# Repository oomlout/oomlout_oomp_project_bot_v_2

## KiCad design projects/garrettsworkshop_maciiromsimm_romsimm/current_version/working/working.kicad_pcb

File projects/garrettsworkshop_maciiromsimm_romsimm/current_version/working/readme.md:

# maciiromsimm
 
## summary 
* id: garrettsworkshop_maciiromsimm_romsimm
* user: garrettsworkshop
* name: maciiromsimm
* board: romsimm
* repo: https://github.com/garrettsworkshop/MacIIROMSIMM
* src_file_repo_kicad_pcb: ROMSIMM.kicad_pcb
* src_file_repo_kicad_pcb_link: https://github.com/garrettsworkshop/MacIIROMSIMM/tree/release-4402A/ROMSIMM.kicad_pcb

* src_file_repo_sch: ROMSIMM.sch
* src_file_repo_sch_link: https://github.com/garrettsworkshop/MacIIROMSIMM/tree/release-4402A/ROMSIMM.sch
* full details link: https://github.com/oomlout/oomlout_oomp_project_bot_v_2/tree/main/projects/garrettsworkshop_maciiromsimm_romsimm/current_version/working

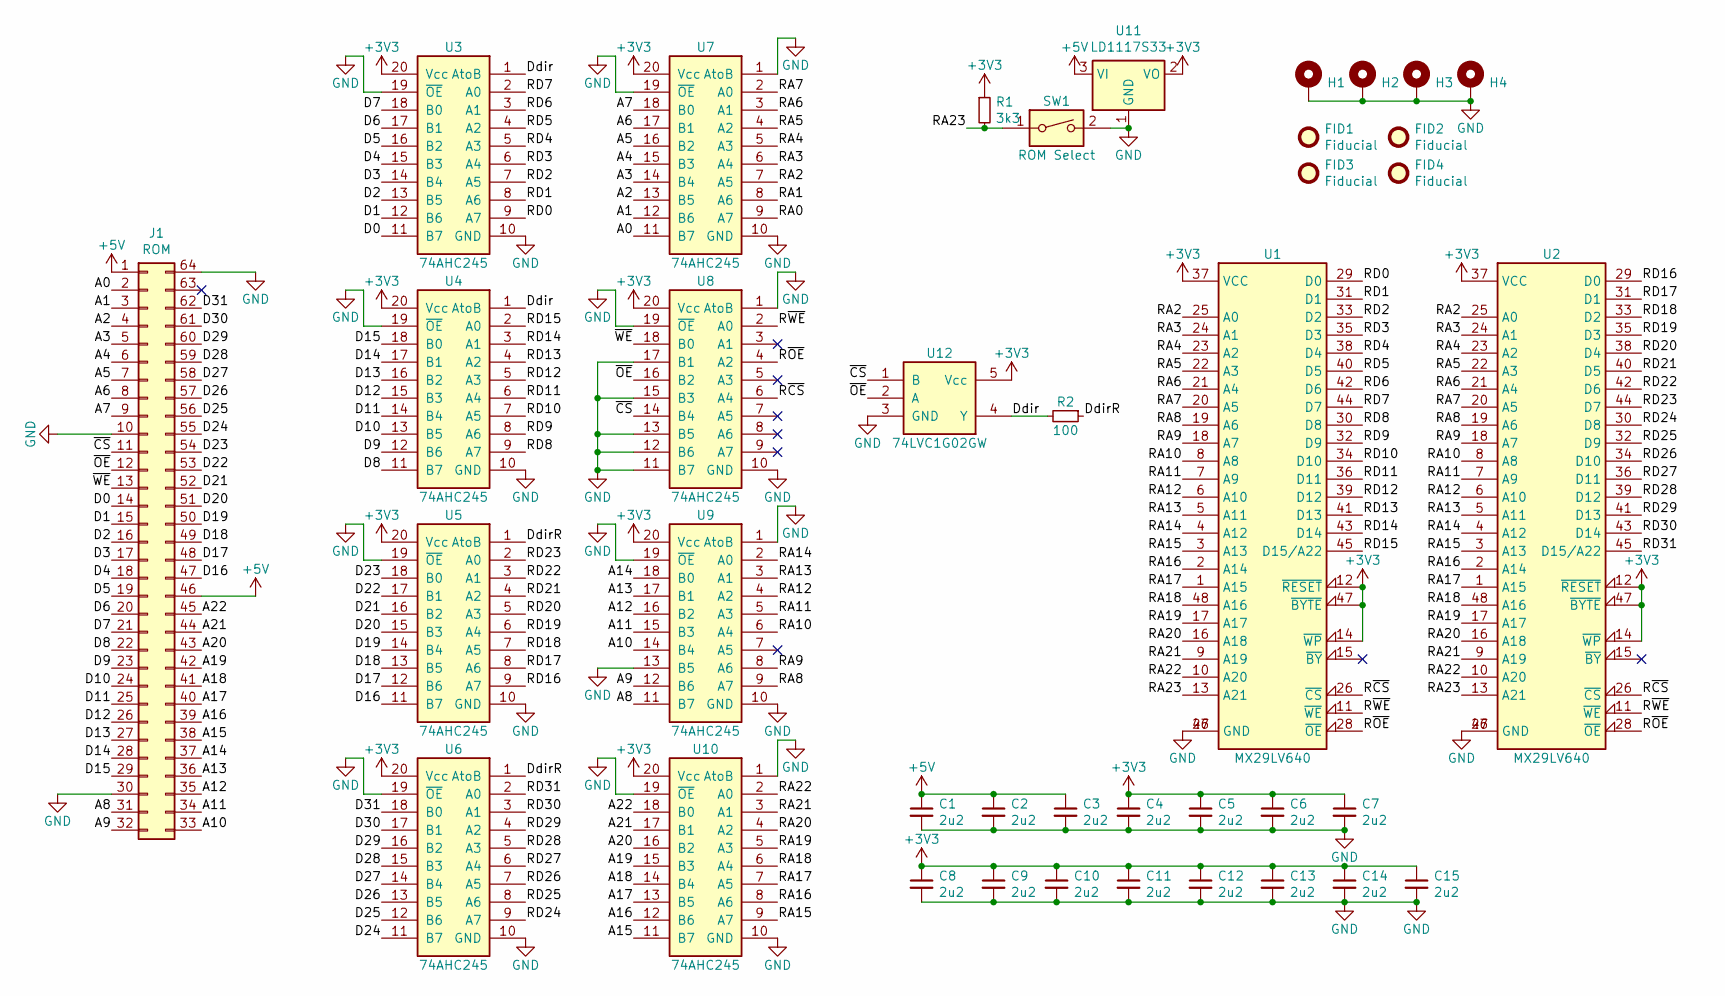
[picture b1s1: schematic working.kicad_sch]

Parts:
C1, C2, C3, C4, C5, C6, C7, C8, C9, C10, C11, C12, C13, C14, C15: 2u2; C_0603
FID1, FID2, FID3, FID4: Fiducial
H1, H2, H3, H4: PasteHole_1.1mm_PTH
J1: ROM; MacIIROMSIMM_Edge
R1: 3k3; R_0805
R2: 100; R_0805
SW1: ROM Select; SW_DIP_SPSTx01_Slide_6.7x4.1mm_W8.61mm_P2.54mm_LowProfile
U1, U2: MX29LV640; TSOP-I-48_18.4x12mm_P0.5mm
U3, U4, U5, U6, U7, U8, U9, U10: 74AHC245; TSSOP-20_4.4x6.5mm_P0.65mm
U11: LD1117S33; SOT-223
U12: 74LVC1G02GW; SOT-353

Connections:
+3V3: C4.1, C5.1, C6.1, C7.1, C8.1, C9.1, C10.1, C11.1, C12.1, C13.1, C14.1, C15.1, R1.1, U1.12 (~RESET), U1.14 (~WP), U1.37 (VCC), U1.47 (~BYTE), U2.12 (~RESET), U2.14 (~WP), U2.37 (VCC), U2.47 (~BYTE), U3.20 (Vcc), U4.20 (Vcc), U5.20 (Vcc), U6.20 (Vcc), U7.20 (Vcc), U8.20 (Vcc), U9.20 (Vcc), U10.20 (Vcc), U11.2 (VO), U12.5 (Vcc)
+5V: C1.1, C2.1, C3.1, J1.1, J1.46, U11.3 (VI)
/A0: J1.2, U7.11 (B7)
/A1: J1.3, U7.12 (B6)
/A2: J1.4, U7.13 (B5)
/A3: J1.5, U7.14 (B4)
/A4: J1.6, U7.15 (B3)
/A5: J1.7, U7.16 (B2)
/A6: J1.8, U7.17 (B1)
/A7: J1.9, U7.18 (B0)
/A8: J1.31, U9.11 (B7)
/A9: J1.32, U9.12 (B6)
/A10: J1.33, U9.14 (B4)
/A11: J1.34, U9.15 (B3)
/A12: J1.35, U9.16 (B2)
/A13: J1.36, U9.17 (B1)
/A14: J1.37, U9.18 (B0)
/A15: J1.38, U10.11 (B7)
/A16: J1.39, U10.12 (B6)
/A17: J1.40, U10.13 (B5)
/A18: J1.41, U10.14 (B4)
/A19: J1.42, U10.15 (B3)
/A20: J1.43, U10.16 (B2)
/A21: J1.44, U10.17 (B1)
/A22: J1.45, U10.18 (B0)
/D0: J1.14, U3.11 (B7)
/D1: J1.15, U3.12 (B6)
/D2: J1.16, U3.13 (B5)
/D3: J1.17, U3.14 (B4)
/D4: J1.18, U3.15 (B3)
/D5: J1.19, U3.16 (B2)
/D6: J1.20, U3.17 (B1)
/D7: J1.21, U3.18 (B0)
/D8: J1.22, U4.11 (B7)
/D9: J1.23, U4.12 (B6)
/D10: J1.24, U4.13 (B5)
/D11: J1.25, U4.14 (B4)
/D12: J1.26, U4.15 (B3)
/D13: J1.27, U4.16 (B2)
/D14: J1.28, U4.17 (B1)
/D15: J1.29, U4.18 (B0)
/D16: J1.47, U5.11 (B7)
/D17: J1.48, U5.12 (B6)
/D18: J1.49, U5.13 (B5)
/D19: J1.50, U5.14 (B4)
/D20: J1.51, U5.15 (B3)
/D21: J1.52, U5.16 (B2)
/D22: J1.53, U5.17 (B1)
/D23: J1.54, U5.18 (B0)
/D24: J1.55, U6.11 (B7)
/D25: J1.56, U6.12 (B6)
/D26: J1.57, U6.13 (B5)
/D27: J1.58, U6.14 (B4)
/D28: J1.59, U6.15 (B3)
/D29: J1.60, U6.16 (B2)
/D30: J1.61, U6.17 (B1)
/D31: J1.62, U6.18 (B0)
/Ddir: R2.2, U3.1 (AtoB), U4.1 (AtoB), U12.4 (Y)
/DdirR: R2.1, U5.1 (AtoB), U6.1 (AtoB)
/RA0: U7.9 (A7)
/RA1: U7.8 (A6)
/RA2: U1.25 (A0), U2.25 (A0), U7.7 (A5)
/RA3: U1.24 (A1), U2.24 (A1), U7.6 (A4)
/RA4: U1.23 (A2), U2.23 (A2), U7.5 (A3)
/RA5: U1.22 (A3), U2.22 (A3), U7.4 (A2)
/RA6: U1.21 (A4), U2.21 (A4), U7.3 (A1)
/RA7: U1.20 (A5), U2.20 (A5), U7.2 (A0)
/RA8: U1.19 (A6), U2.19 (A6), U9.9 (A7)
/RA9: U1.18 (A7), U2.18 (A7), U9.8 (A6)
/RA10: U1.8 (A8), U2.8 (A8), U9.6 (A4)
/RA11: U1.7 (A9), U2.7 (A9), U9.5 (A3)
/RA12: U1.6 (A10), U2.6 (A10), U9.4 (A2)
/RA13: U1.5 (A11), U2.5 (A11), U9.3 (A1)
/RA14: U1.4 (A12), U2.4 (A12), U9.2 (A0)
/RA15: U1.3 (A13), U2.3 (A13), U10.9 (A7)
/RA16: U1.2 (A14), U2.2 (A14), U10.8 (A6)
/RA17: U1.1 (A15), U2.1 (A15), U10.7 (A5)
/RA18: U1.48 (A16), U2.48 (A16), U10.6 (A4)
/RA19: U1.17 (A17), U2.17 (A17), U10.5 (A3)
/RA20: U1.16 (A18), U2.16 (A18), U10.4 (A2)
/RA21: U1.9 (A19), U2.9 (A19), U10.3 (A1)
/RA22: U1.10 (A20), U2.10 (A20), U10.2 (A0)
/RA23: R1.2, SW1.1, U1.13 (A21), U2.13 (A21)
/RD0: U1.29 (D0), U3.9 (A7)
/RD1: U1.31 (D1), U3.8 (A6)
/RD2: U1.33 (D2), U3.7 (A5)
/RD3: U1.35 (D3), U3.6 (A4)
/RD4: U1.38 (D4), U3.5 (A3)
/RD5: U1.40 (D5), U3.4 (A2)
/RD6: U1.42 (D6), U3.3 (A1)
/RD7: U1.44 (D7), U3.2 (A0)
/RD8: U1.30 (D8), U4.9 (A7)
/RD9: U1.32 (D9), U4.8 (A6)
/RD10: U1.34 (D10), U4.7 (A5)
/RD11: U1.36 (D11), U4.6 (A4)
/RD12: U1.39 (D12), U4.5 (A3)
/RD13: U1.41 (D13), U4.4 (A2)
/RD14: U1.43 (D14), U4.3 (A1)
/RD15: U1.45 (D15/A22), U4.2 (A0)
/RD16: U2.29 (D0), U5.9 (A7)
/RD17: U2.31 (D1), U5.8 (A6)
/RD18: U2.33 (D2), U5.7 (A5)
/RD19: U2.35 (D3), U5.6 (A4)
/RD20: U2.38 (D4), U5.5 (A3)
/RD21: U2.40 (D5), U5.4 (A2)
/RD22: U2.42 (D6), U5.3 (A1)
/RD23: U2.44 (D7), U5.2 (A0)
/RD24: U2.30 (D8), U6.9 (A7)
/RD25: U2.32 (D9), U6.8 (A6)
/RD26: U2.34 (D10), U6.7 (A5)
/RD27: U2.36 (D11), U6.6 (A4)
/RD28: U2.39 (D12), U6.5 (A3)
/RD29: U2.41 (D13), U6.4 (A2)
/RD30: U2.43 (D14), U6.3 (A1)
/RD31: U2.45 (D15/A22), U6.2 (A0)
/R~CS: U1.26 (~CS), U2.26 (~CS), U8.6 (A4)
/R~OE: U1.28 (~OE), U2.28 (~OE), U8.4 (A2)
/R~WE: U1.11 (~WE), U2.11 (~WE), U8.2 (A0)
/~CS: J1.11, U8.14 (B4), U12.1 (B)
/~OE: J1.12, U8.16 (B2), U12.2 (A)
/~WE: J1.13, U8.18 (B0)
GND: C1.2, C2.2, C3.2, C4.2, C5.2, C6.2, C7.2, C8.2, C9.2, C10.2, C11.2, C12.2, C13.2, C14.2, C15.2, H1.1, H2.1, H3.1, H4.1, J1.10, J1.30, J1.64, SW1.2, U1.27 (GND), U1.46 (GND), U2.27 (GND), U2.46 (GND), U3.10 (GND), U3.19 (~OE), U4.10 (GND), U4.19 (~OE), U5.10 (GND), U5.19 (~OE), U6.10 (GND), U6.19 (~OE), U7.1 (AtoB), U7.10 (GND), U7.19 (~OE), U8.1 (AtoB), U8.10 (GND), U8.11 (B7), U8.12 (B6), U8.13 (B5), U8.15 (B3), U8.17 (B1), U8.19 (~OE), U9.1 (AtoB), U9.10 (GND), U9.13 (B5), U9.19 (~OE), U10.1 (AtoB), U10.10 (GND), U10.19 (~OE), U11.1 (GND), U12.3 (GND)

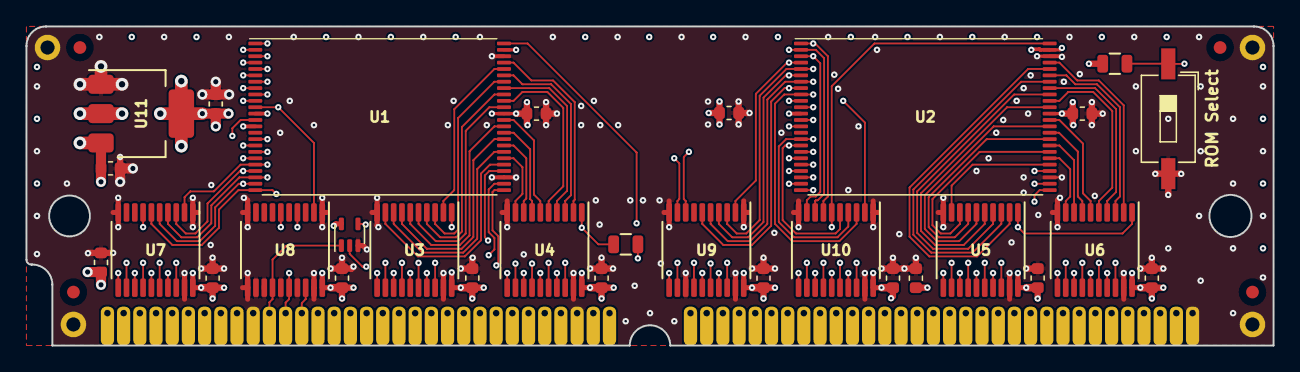
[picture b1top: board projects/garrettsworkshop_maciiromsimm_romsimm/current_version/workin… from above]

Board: 4 copper layers, 97.8 x 25.0 mm, 39 parts (0 on the bottom side), 120 nets.

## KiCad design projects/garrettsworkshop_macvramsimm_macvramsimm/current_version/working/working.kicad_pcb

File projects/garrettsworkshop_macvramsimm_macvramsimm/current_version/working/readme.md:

# macvramsimm
 
## summary 
* id: garrettsworkshop_macvramsimm_macvramsimm
* user: garrettsworkshop
* name: macvramsimm
* board: macvramsimm
* repo: https://github.com/garrettsworkshop/MacVRAMSIMM
* src_file_repo_kicad_pcb: 512kB-2chip-SOJ/MacVRAMSIMM.kicad_pcb
* src_file_repo_kicad_pcb_link: https://github.com/garrettsworkshop/MacVRAMSIMM/tree/dev/512kB-2chip-SOJ/MacVRAMSIMM.kicad_pcb
* src_file_repo_kicad_sch: 512kB-2chip-SOJ/MacVRAMSIMM.kicad_sch
* src_file_repo_kicad_sch_link: https://github.com/garrettsworkshop/MacVRAMSIMM/tree/dev/512kB-2chip-SOJ/MacVRAMSIMM.kicad_sch

* src_file_repo_sch: 256kB-2chip-SOJ/MacVRAMSIMM.sch
* src_file_repo_sch_link: https://github.com/garrettsworkshop/MacVRAMSIMM/tree/dev/256kB-2chip-SOJ/MacVRAMSIMM.sch
* full details link: https://github.com/oomlout/oomlout_oomp_project_bot_v_2/tree/main/projects/garrettsworkshop_macvramsimm_macvramsimm/current_version/working

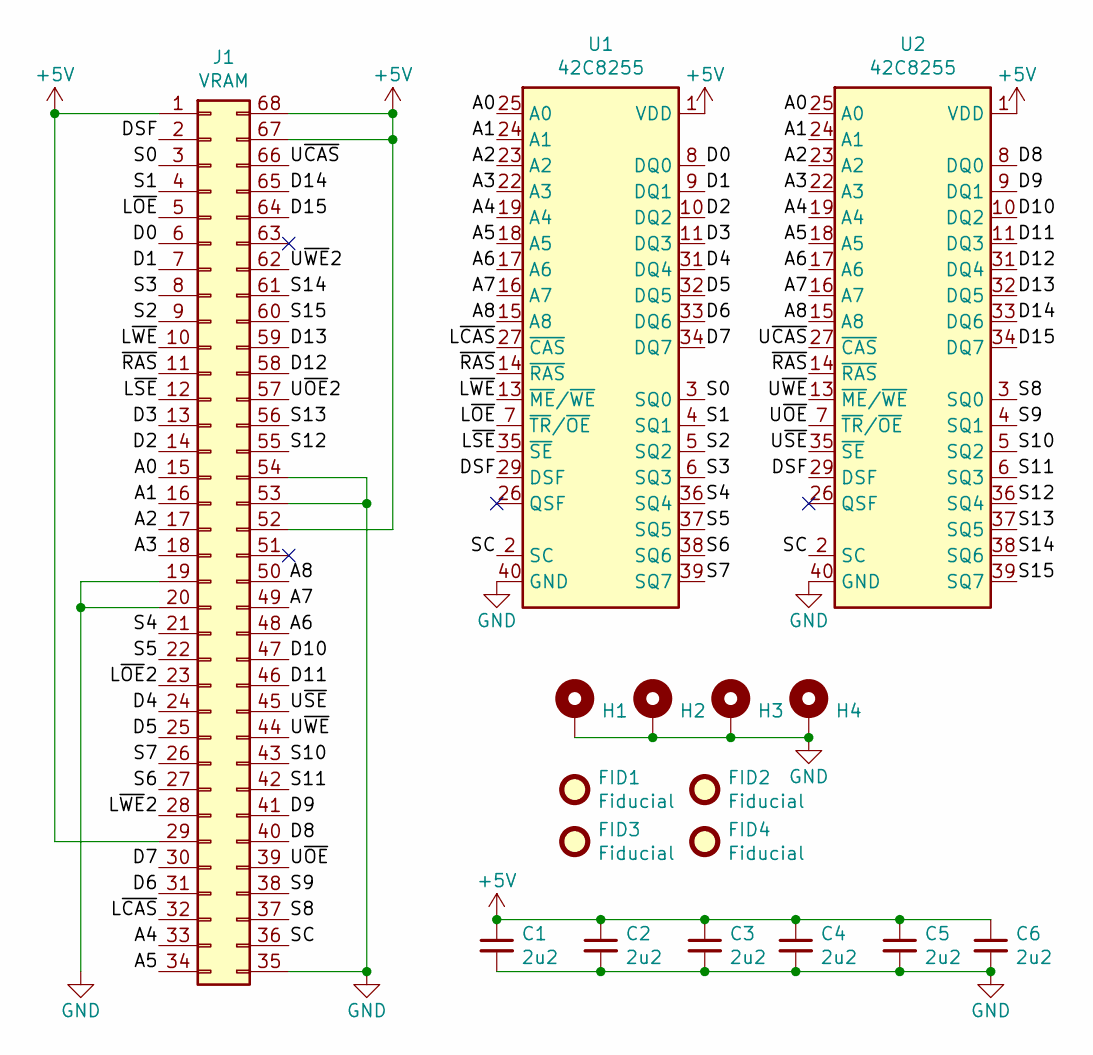
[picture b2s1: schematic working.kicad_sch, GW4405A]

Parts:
C1, C2, C3, C4, C5, C6: 2u2; C_0805
FID1, FID2, FID3, FID4: Fiducial
H1, H2, H3, H4: PasteHole_1.1mm_PTH
J1: VRAM; MacVRAMSIMM_Edge
U1, U2: 42C8255; SOJ-40_400mil

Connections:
+5V: C1.1, C2.1, C3.1, C4.1, C5.1, C6.1, J1.1, J1.29, J1.52, J1.67, J1.68, U1.1 (VDD), U1.20 (VDD), U2.1 (VDD), U2.20 (VDD)
/A0: J1.15, U1.25 (A0), U2.25 (A0)
/A1: J1.16, U1.24 (A1), U2.24 (A1)
/A2: J1.17, U1.23 (A2), U2.23 (A2)
/A3: J1.18, U1.22 (A3), U2.22 (A3)
/A4: J1.33, U1.19 (A4), U2.19 (A4)
/A5: J1.34, U1.18 (A5), U2.18 (A5)
/A6: J1.48, U1.17 (A6), U2.17 (A6)
/A7: J1.49, U1.16 (A7), U2.16 (A7)
/A8: J1.50, U1.15 (A8), U2.15 (A8)
/D0: J1.6, U1.8 (DQ0)
/D1: J1.7, U1.9 (DQ1)
/D2: J1.14, U1.10 (DQ2)
/D3: J1.13, U1.11 (DQ3)
/D4: J1.24, U1.31 (DQ4)
/D5: J1.25, U1.32 (DQ5)
/D6: J1.31, U1.33 (DQ6)
/D7: J1.30, U1.34 (DQ7)
/D8: J1.40, U2.8 (DQ0)
/D9: J1.41, U2.9 (DQ1)
/D10: J1.47, U2.10 (DQ2)
/D11: J1.46, U2.11 (DQ3)
/D12: J1.58, U2.31 (DQ4)
/D13: J1.59, U2.32 (DQ5)
/D14: J1.65, U2.33 (DQ6)
/D15: J1.64, U2.34 (DQ7)
/DSF: J1.2, U1.29 (DSF), U2.29 (DSF)
/L~CAS: J1.32, U1.27 (~CAS)
/L~OE: J1.5, U1.7 (~TR/~OE)
/L~OE2: J1.23
/L~SE: J1.12, U1.35 (~SE)
/L~WE: J1.10, U1.13 (~ME/~WE)
/L~WE2: J1.28
/S0: J1.3, U1.3 (SQ0)
/S1: J1.4, U1.4 (SQ1)
/S2: J1.9, U1.5 (SQ2)
/S3: J1.8, U1.6 (SQ3)
/S4: J1.21, U1.36 (SQ4)
/S5: J1.22, U1.37 (SQ5)
/S6: J1.27, U1.38 (SQ6)
/S7: J1.26, U1.39 (SQ7)
/S8: J1.37, U2.3 (SQ0)
/S9: J1.38, U2.4 (SQ1)
/S10: J1.43, U2.5 (SQ2)
/S11: J1.42, U2.6 (SQ3)
/S12: J1.55, U2.36 (SQ4)
/S13: J1.56, U2.37 (SQ5)
/S14: J1.61, U2.38 (SQ6)
/S15: J1.60, U2.39 (SQ7)
/SC: J1.36, U1.2 (SC), U2.2 (SC)
/U~CAS: J1.66, U2.27 (~CAS)
/U~OE: J1.39, U2.7 (~TR/~OE)
/U~OE2: J1.57
/U~SE: J1.45, U2.35 (~SE)
/U~WE: J1.44, U2.13 (~ME/~WE)
/U~WE2: J1.62
/~RAS: J1.11, U1.14 (~RAS), U2.14 (~RAS)
GND: C1.2, C2.2, C3.2, C4.2, C5.2, C6.2, H1.1, H2.1, H3.1, H4.1, J1.19, J1.20, J1.35, J1.53, J1.54, U1.12 (GND), U1.21 (GND), U1.30 (GND), U1.40 (GND), U2.12 (GND), U2.21 (GND), U2.30 (GND), U2.40 (GND)

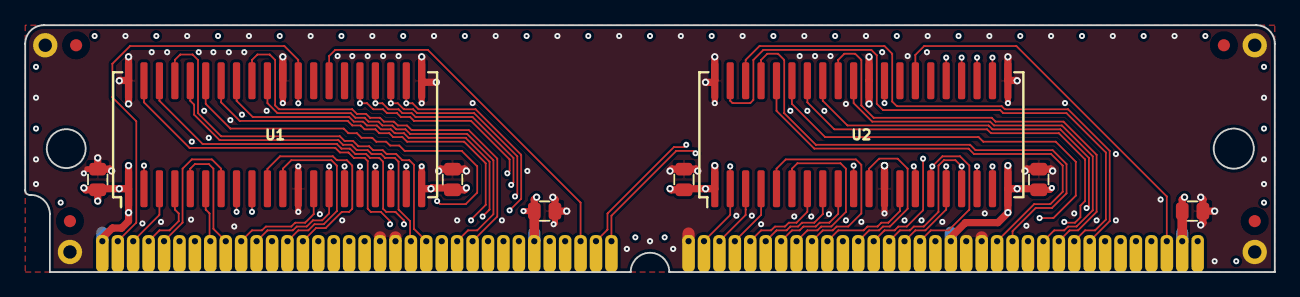
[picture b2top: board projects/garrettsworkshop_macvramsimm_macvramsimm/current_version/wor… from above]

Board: 4 copper layers, 102.9 x 20.3 mm, 17 parts (0 on the bottom side), 54 nets.

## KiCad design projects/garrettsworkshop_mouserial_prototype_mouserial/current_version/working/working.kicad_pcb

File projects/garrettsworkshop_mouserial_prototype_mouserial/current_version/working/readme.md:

# mouserial_prototype
 
## summary 
* id: garrettsworkshop_mouserial_prototype_mouserial
* user: garrettsworkshop
* name: mouserial_prototype
* board: mouserial
* repo: https://github.com/garrettsworkshop/Mouserial-prototype
* src_file_repo_kicad_pcb: Mouserial.kicad_pcb
* src_file_repo_kicad_pcb_link: https://github.com/garrettsworkshop/Mouserial-prototype/tree/dev/Mouserial.kicad_pcb

* src_file_repo_sch: 
* src_file_repo_sch_link: https://github.com/garrettsworkshop/Mouserial-prototype/tree/dev/
* full details link: https://github.com/oomlout/oomlout_oomp_project_bot_v_2/tree/main/projects/garrettsworkshop_mouserial_prototype_mouserial/current_version/working

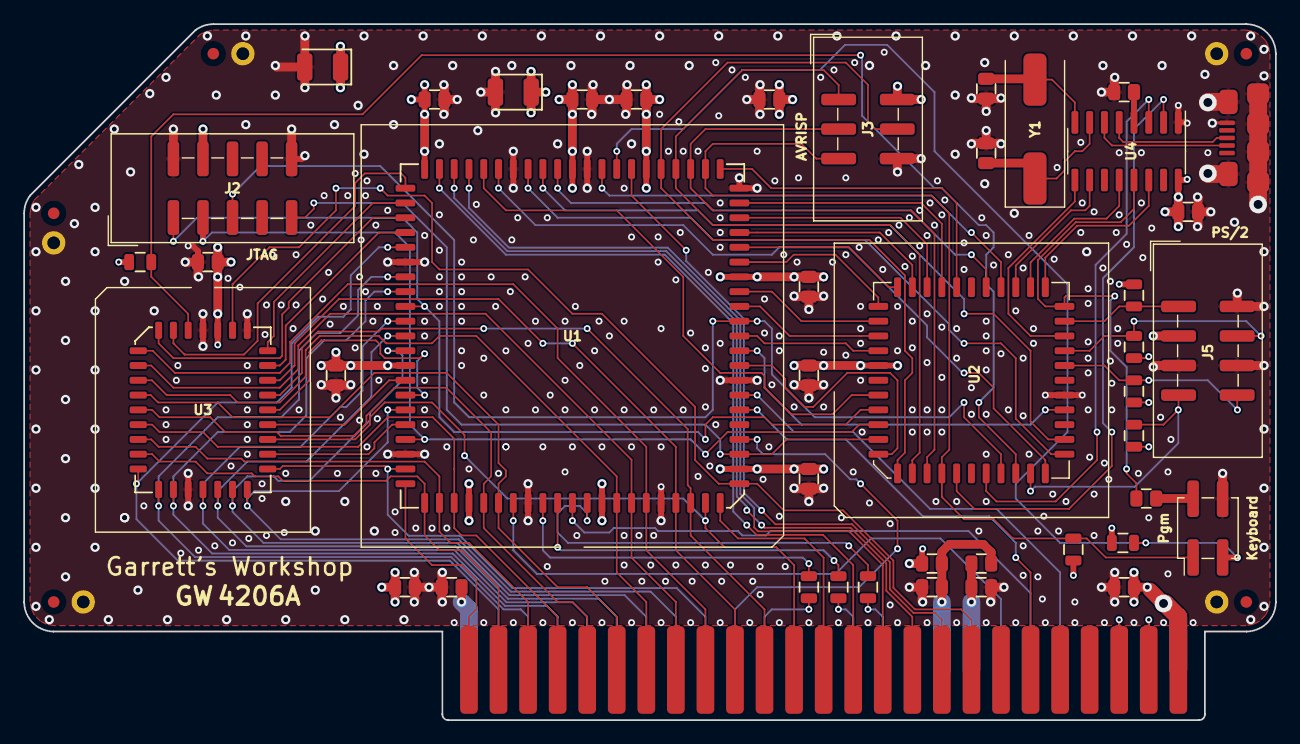
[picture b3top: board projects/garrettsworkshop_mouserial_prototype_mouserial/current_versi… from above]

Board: 4 copper layers, 107.6 x 59.8 mm, 54 parts (0 on the bottom side), 95 nets.

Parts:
C1, C2, C3, C4, C5, C6, C7, C8, C9, C10, C11, C12, C13, C14, C15, C17, C19, C21, C22: 100n; C_0805
C16, C23: 33u; CP_EIA-3528
C18, C20: 22p; C_0805
FID1, FID2, FID3, FID4, FID5: Fiducial
H1, H2, H3, H4, H5: PasteHole_1.1mm_PTH
J1: AppleIIBus; AppleIIBus_Edge
J2: JTAG; IDC_SMD_2x05_P2.54mm_Vertical
J3: AVRISP; IDC_SMD_2x03_P2.54mm_Vertical
J4: USBmicroB; USB_Micro-B_Amphenol_10118192-0001
J5: PS/2; IDC_SMD_2x04_P2.54mm_Vertical
JP1: P/K; PinHeader_2x02_P2.54mm_Vertical_SMD
R1, R2, R3, R7, R8, R9, R10: 4k7; R_0805
R4, R5, R6: 100; R_0805
U1: EPM7128SL84; PLCC-84_SMDSocket
U2: ATmega8515L-8JU; PLCC-44_SMDSocket
U3: 39SF010; PLCC-32_SMDSocket
U4: CH340G; SOIC-16_3.9mm
Y1: 12M; Crystal_HC49-SMD

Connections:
+3V3: C19.1, U4.4
+5V: C1.1, C2.1, C3.1, C4.1, C5.1, C6.1, C7.1, C8.1, C9.1, C10.1, C11.1, C14.1, C16.1, C17.1, C23.1, J1.25, J2.4, J3.2, J5.3, R1.1, R2.1, R3.1, R7.1, R8.1, R9.1, R10.1, U1.3, U1.13, U1.26, U1.38, U1.43, U1.53, U1.66, U1.78, U2.44, U3.32, U4.16
+12V: C12.1, J1.50
-5V: C15.2, C17.2, C22.1, J1.34
-12V: C13.2, C22.2, J1.33
/7M: J1.36, R4.2
/7Mr: R4.1, U1.2
/A0: J1.2, U1.75, U3.12
/A1: J1.3, U1.76, U3.11
/A2: J1.4, U1.77, U3.10
/A3: J1.5, U1.79, U3.9
/A4: J1.6, U1.80, U3.8
/A5: J1.7, U1.4, U3.7
/A6: J1.8, U1.5, U3.6
/A7: J1.9, U1.6, U3.5
/A8: J1.10, U1.8, U3.27
/A9: J1.11, U1.9, U3.26
/A10: J1.12, U1.10, U3.23
/A11: J1.13, U1.11
/A12: J1.14, U1.52
/A13: J1.15, U1.51
/A14: J1.16, U1.50
/A15: J1.17, U1.39
/D0: J1.49, U1.58, U3.13
/D1: J1.48, U1.60, U3.14
/D2: J1.47, U1.61, U3.15
/D3: J1.46, U1.63, U3.17
/D4: J1.45, U1.64, U3.18
/D5: J1.44, U1.65, U3.19
/D6: J1.43, U1.69, U3.20
/D7: J1.42, U1.73, U3.21
/DMAin: J1.24, J1.27
/INTin: J1.23, J1.28
/KClk: J5.4, R9.2, U2.25
/KDat: J5.8, R8.2, U2.24
/MClk: J5.1, R3.2, U2.27
/MDat: J5.7, R2.2, U2.16
/MISO: J3.1, U1.36, U2.8
/MOSI: J3.4, U1.37, U2.7
/PHI0: J1.40, R5.2
/PHI0r: R5.1, U1.83
/Q3: J1.37, R6.2
/Q3r: R6.1, U1.84
/RAD0: U1.22, U2.43
/RAD1: U1.24, U2.42
/RAD2: U1.25, U2.41
/RAD3: U1.27, U2.40
/RAD4: U1.28, U2.39
/RAD5: U1.29, U2.38
/RAD6: U1.30, U2.37
/RAD7: U1.31, U2.36
/RALE: U1.44, U2.33
/RClk: U1.21, U2.21
/ROMA11: U1.68, U3.25
/ROMA12: U1.56, U3.4
/ROMA13: U1.57, U3.28
/ROMA14: U1.55, U3.29
/ROMA15: U1.54, U3.3
/ROMA16: R7.2, U2.15, U3.2
/RXD: U2.11, U4.2
/R~CS: U1.70, U3.22
/R~IRQ: U1.33, U2.35
/R~OE: U1.67, U3.24
/R~RD: U1.45, U2.19
/R~RST: J3.5, JP1.1, R1.2, U1.34, U2.10
/R~WR: U1.46, U2.18
/R~W: J1.18, U1.12, U3.31
/SCK: J3.3, U1.35, U2.9
/T0: U1.49, U2.2
/TCK: J2.1, U1.62, U2.3
/TDI: J2.9, U1.14, U2.5
/TDO: J2.3, U1.71, U2.4
/TMS: J2.5, U1.23, U2.14
/TXD: U2.13, U4.3
/VBl0: U1.48, U2.17
/VBl1: U1.41, U2.32
/~CTS: U2.26, U4.9
/~DCD: U2.30, U4.12
/~DEVSEL: J1.41, U1.15
/~DSR: U2.31, U4.10
/~DTR: C21.1, U2.28, U4.13
/~INH: J1.32, U1.81
/~IOSEL: J1.1, U1.74
/~IOSTRB: J1.20, U1.17
/~IRQ: J1.30, U1.18
/~KMode: JP1.3, R10.2, U1.40
/~RES: J1.31, U1.1
/~RTS: U2.29, U4.14
/~SS: U1.20, U2.6
GND: C1.2, C2.2, C3.2, C4.2, C5.2, C6.2, C7.2, C8.2, C9.2, C10.2, C11.2, C12.2, C13.1, C14.2, C15.1, C16.2, C18.2, C19.2, C20.2, C23.2, H1.1, H2.1, H3.1, H4.1, H5.1, J1.26, J2.2, J2.10, J3.6, J4.5, J4.6, J5.2, J5.5, J5.6, JP1.4, U1.7, U1.19, U1.32, U1.42, U1.47, U1.59, U1.72, U1.82, U2.22, U3.1, U3.16, U3.30, U4.1
unnamed: C18.1, U4.8, Y1.2
unnamed: C20.1, U4.7, Y1.1
unnamed: C21.2, JP1.2
unnamed: J4.2, U4.6
unnamed: J4.3, U4.5

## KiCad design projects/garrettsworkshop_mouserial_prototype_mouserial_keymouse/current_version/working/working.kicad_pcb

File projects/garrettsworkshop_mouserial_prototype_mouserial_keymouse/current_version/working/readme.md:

# mouserial_prototype
 
## summary 
* id: garrettsworkshop_mouserial_prototype_mouserial_keymouse
* user: garrettsworkshop
* name: mouserial_prototype
* board: mouserial_keymouse
* repo: https://github.com/garrettsworkshop/Mouserial-prototype
* src_file_repo_kicad_pcb: adapter-keymouse/mouserial-keymouse.kicad_pcb
* src_file_repo_kicad_pcb_link: https://github.com/garrettsworkshop/Mouserial-prototype/tree/dev/adapter-keymouse/mouserial-keymouse.kicad_pcb

* src_file_repo_sch: adapter-keymouse/mouserial-keymouse.sch
* src_file_repo_sch_link: https://github.com/garrettsworkshop/Mouserial-prototype/tree/dev/adapter-keymouse/mouserial-keymouse.sch
* full details link: https://github.com/oomlout/oomlout_oomp_project_bot_v_2/tree/main/projects/garrettsworkshop_mouserial_prototype_mouserial_keymouse/current_version/working

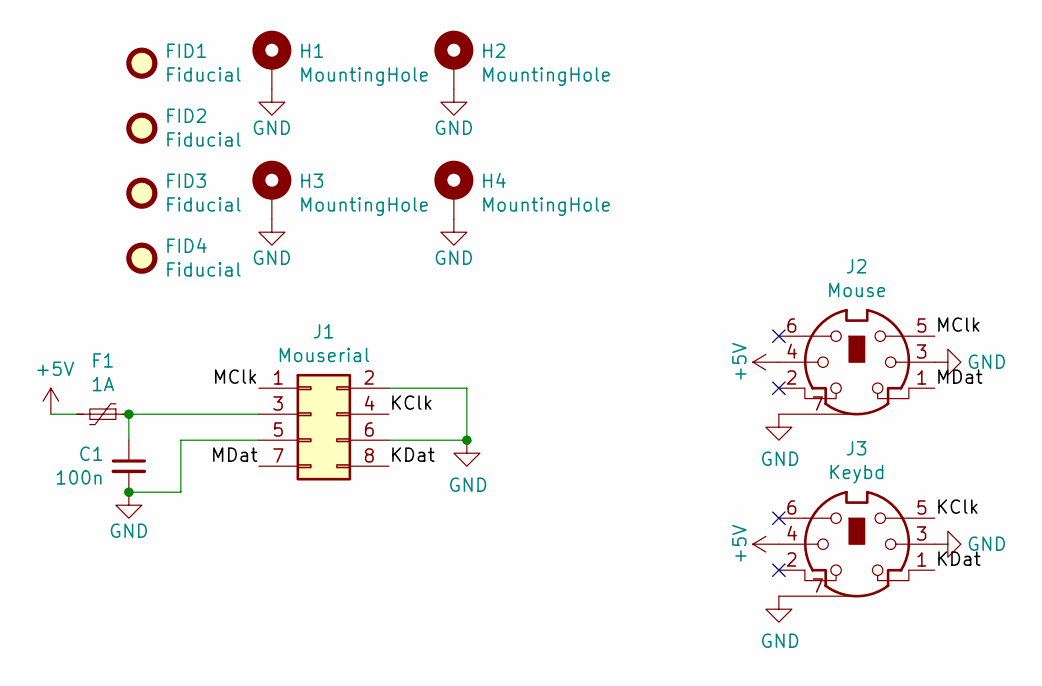
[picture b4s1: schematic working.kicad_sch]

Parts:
C1: 100n; C_0805
F1: 1A; BelFuse_1206
FID1, FID2, FID3, FID4: Fiducial
H1, H2, H3, H4: MountingHole; PasteHole_1.05mm_PTH
J1: Mouserial; IDC_SMD_2x04_P2.54mm_Vertical
J2: Mouse; MD-60
J3: Keybd; MD-60

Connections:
+5V: F1.2, J2.4, J3.4
/KClk: J1.4, J3.5
/KDat: J1.8, J3.1
/MClk: J1.1, J2.5
/MDat: J1.7, J2.1
GND: C1.2, H1.1, H2.1, H3.1, H4.1, J1.2, J1.5, J1.6, J2.3, J2.7, J3.3, J3.7
unnamed: C1.1, F1.1, J1.3

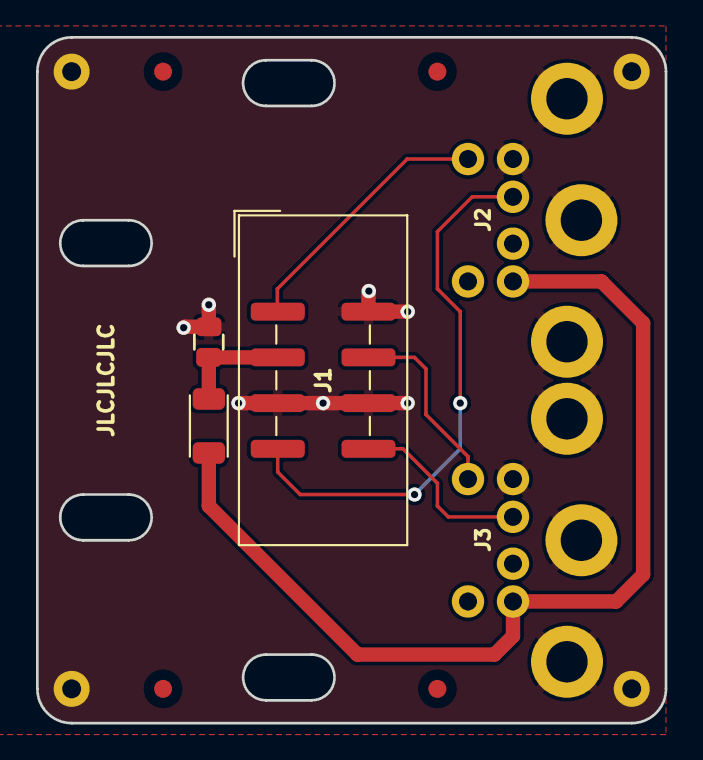
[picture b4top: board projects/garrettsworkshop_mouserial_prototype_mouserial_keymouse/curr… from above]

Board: 2 copper layers, 34.9 x 38.1 mm, 13 parts (0 on the bottom side), 7 nets.

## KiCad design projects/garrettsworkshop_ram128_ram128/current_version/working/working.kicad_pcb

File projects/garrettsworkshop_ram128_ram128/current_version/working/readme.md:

# ram128
 
## summary 
* id: garrettsworkshop_ram128_ram128
* user: garrettsworkshop
* name: ram128
* board: ram128
* repo: https://github.com/garrettsworkshop/RAM128
* src_file_repo_kicad_pcb: RAM128.kicad_pcb
* src_file_repo_kicad_pcb_link: https://github.com/garrettsworkshop/RAM128/tree/release-GW4208B/RAM128.kicad_pcb
* src_file_repo_kicad_sch: RAM128.kicad_sch
* src_file_repo_kicad_sch_link: https://github.com/garrettsworkshop/RAM128/tree/release-GW4208B/RAM128.kicad_sch

* src_file_repo_sch: 
* src_file_repo_sch_link: https://github.com/garrettsworkshop/RAM128/tree/release-GW4208B/
* full details link: https://github.com/oomlout/oomlout_oomp_project_bot_v_2/tree/main/projects/garrettsworkshop_ram128_ram128/current_version/working

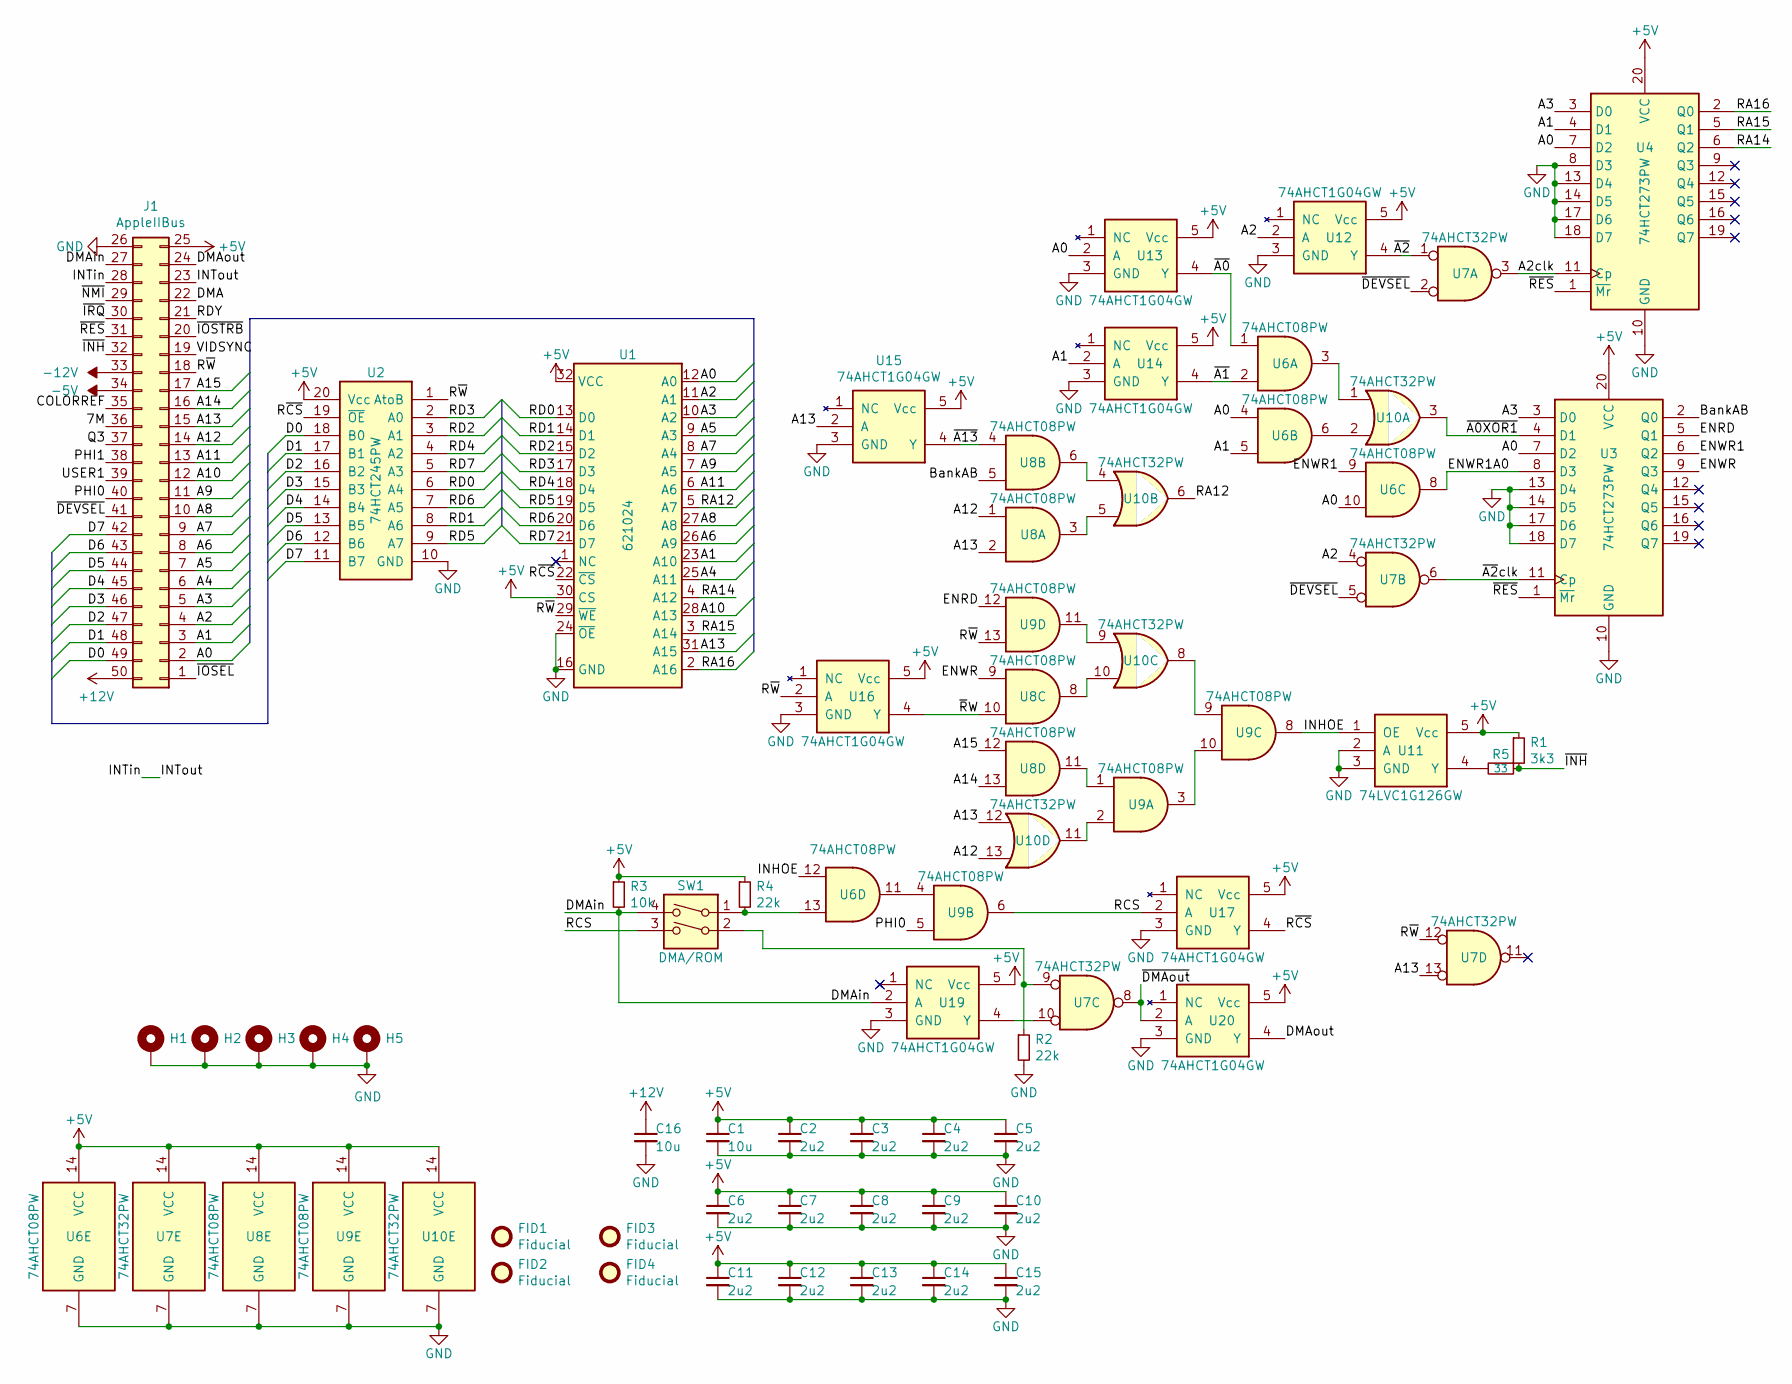
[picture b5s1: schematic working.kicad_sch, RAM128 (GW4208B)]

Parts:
C1, C16: 10u; C_0805; LCSC Part C15850
C2, C3, C4, C5, C6, C7, C8, C9, C10, C11, C12, C13, C14, C15: 2u2; C_0603; LCSC Part C23630
FID1, FID2, FID3, FID4: Fiducial
H1, H2, H3, H4, H5: PasteHole_1.152mm_NPTH
J1: AppleIIBus; AppleIIBus_Edge
R1: 3k3; R_0805; LCSC Part C26010
R2, R4: 22k; R_0805; LCSC Part C17560
R3: 10k; R_0805; LCSC Part C17414
R5: 33; R_0805; LCSC Part C17634
SW1: DMA/ROM; SW_DIP_SPSTx02_Slide_DSHP02TS_P1.27mm; LCSC Part C319052
U1: 621024; SOP-32_450mil; LCSC Part C397875
U2: 74HCT245PW; TSSOP-20_4.4x6.5mm_P0.65mm; LCSC Part C5980
U3, U4: 74HCT273PW; TSSOP-20_4.4x6.5mm_P0.65mm; LCSC Part C5983
U6, U8, U9: 74AHCT08PW; TSSOP-14_4.4x5mm_P0.65mm; LCSC Part C155175
U7, U10: 74AHCT32PW; TSSOP-14_4.4x5mm_P0.65mm; LCSC Part C129435
U11: 74LVC1G126GW; SOT-353; LCSC Part C88039
U12, U13, U14, U15, U16, U17, U19, U20: 74AHCT1G04GW; SOT-353; LCSC Part C148199

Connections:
+5V: C1.1, C2.1, C3.1, C4.1, C5.1, C6.1, C7.1, C8.1, C9.1, C10.1, C11.1, C12.1, C13.1, C14.1, C15.1, J1.25, R1.1, R3.1, R4.1, U1.30 (CS), U1.32 (VCC), U2.20 (Vcc), U3.20 (VCC), U4.20 (VCC), U6.14 (VCC), U7.14 (VCC), U8.14 (VCC), U9.14 (VCC), U10.14 (VCC), U11.5 (Vcc), U12.5 (Vcc), U13.5 (Vcc), U14.5 (Vcc), U15.5 (Vcc), U16.5 (Vcc), U17.5 (Vcc), U19.5 (Vcc), U20.5 (Vcc)
+12V: C16.1, J1.50
-5V: J1.34
-12V: J1.33
/7M: J1.36
/A0: J1.2, U1.12 (A0), U3.7 (D2), U4.7 (D2), U6.4, U6.10, U13.2 (A)
/A1: J1.3, U1.23 (A10), U4.4 (D1), U6.5, U14.2 (A)
/A2: J1.4, U1.11 (A1), U7.4, U12.2 (A)
/A2clk: U4.11 (Cp), U7.3
/A3: J1.5, U1.10 (A2), U3.3 (D0), U4.3 (D0)
/A4: J1.6, U1.25 (A11)
/A5: J1.7, U1.9 (A3)
/A6: J1.8, U1.26 (A9)
/A7: J1.9, U1.8 (A4)
/A8: J1.10, U1.27 (A8)
/A9: J1.11, U1.7 (A5)
/A10: J1.12, U1.28 (A13)
/A11: J1.13, U1.6 (A6)
/A12: J1.14, U8.1, U10.13
/A13: J1.15, U1.31 (A15), U7.13, U8.2, U10.12, U15.2 (A)
/A14: J1.16, U8.13
/A15: J1.17, U8.12
/BankAB: U3.2 (Q0), U8.5
/COLORREF: J1.35
/D0: J1.49, U2.18 (B0)
/D1: J1.48, U2.17 (B1)
/D2: J1.47, U2.16 (B2)
/D3: J1.46, U2.15 (B3)
/D4: J1.45, U2.14 (B4)
/D5: J1.44, U2.13 (B5)
/D6: J1.43, U2.12 (B6)
/D7: J1.42, U2.11 (B7)
/DMA: J1.22
/DMAin: J1.27, R3.2, SW1.4, U19.2 (A)
/DMAout: J1.24, U20.4 (Y)
/ENRD: U3.5 (Q1), U9.12
/ENWR: U3.9 (Q3), U8.9
/ENWR1: U3.6 (Q2), U6.9
/ENWR1A0: U3.8 (D3), U6.8
/INHOE: U6.12, U9.8, U11.1 (OE)
/INTin: J1.23, J1.28
/PHI0: J1.40, U9.5
/PHI1: J1.38
/Q3: J1.37
/RA12: U1.5 (A7), U10.6
/RA14: U1.4 (A12), U4.6 (Q2)
/RA15: U1.3 (A14), U4.5 (Q1)
/RA16: U1.2 (A16), U4.2 (Q0)
/RCS: SW1.3, U9.6, U17.2 (A)
/RD0: U1.13 (D0), U2.6 (A4)
/RD1: U1.14 (D1), U2.8 (A6)
/RD2: U1.15 (D2), U2.3 (A1)
/RD3: U1.17 (D3), U2.2 (A0)
/RD4: U1.18 (D4), U2.4 (A2)
/RD5: U1.19 (D5), U2.9 (A7)
/RD6: U1.20 (D6), U2.7 (A5)
/RD7: U1.21 (D7), U2.5 (A3)
/RDY: J1.21
/R~CS: U1.22 (~CS), U2.19 (~OE), U17.4 (Y)
/R~W: J1.18, U1.29 (~WE), U2.1 (AtoB), U7.12, U9.13, U16.2 (A)
/USER1: J1.39
/VIDSYNC: J1.19
/~A0XOR1: U3.4 (D1), U10.3
/~A0: U6.1, U13.4 (Y)
/~A1: U6.2, U14.4 (Y)
/~A2: U7.1, U12.4 (Y)
/~A2clk: U3.11 (Cp), U7.6
/~A13: U8.4, U15.4 (Y)
/~DEVSEL: J1.41, U7.2, U7.5
/~DMAout: U7.8, U20.2 (A)
/~INH: J1.32, R1.2, R5.1
/~IOSEL: J1.1
/~IOSTRB: J1.20
/~IRQ: J1.30
/~NMI: J1.29
/~RES: J1.31, U3.1 (~Mr), U4.1 (~Mr)
/~RW: U8.10, U16.4 (Y)
GND: C1.2, C2.2, C3.2, C4.2, C5.2, C6.2, C7.2, C8.2, C9.2, C10.2, C11.2, C12.2, C13.2, C14.2, C15.2, C16.2, H1.1, H2.1, H3.1, H4.1, H5.1, J1.26, R2.2, U1.16 (GND), U1.24 (~OE), U2.10 (GND), U3.10 (GND), U3.13 (D4), U3.14 (D5), U3.17 (D6), U3.18 (D7), U4.8 (D3), U4.10 (GND), U4.13 (D4), U4.14 (D5), U4.17 (D6), U4.18 (D7), U6.7 (GND), U7.7 (GND), U8.7 (GND), U9.7 (GND), U10.7 (GND), U11.2 (A), U11.3 (GND), U12.3 (GND), U13.3 (GND), U14.3 (GND), U15.3 (GND), U16.3 (GND), U17.3 (GND), U19.3 (GND), U20.3 (GND)
unnamed: R2.1, SW1.2, U7.9
unnamed: R4.2, SW1.1, U6.13
unnamed: R5.2, U11.4 (Y)
unnamed: U6.11, U9.4
unnamed: U8.11, U9.1
unnamed: U9.3, U9.10
unnamed: U6.3, U10.1
unnamed: U6.6, U10.2
unnamed: U8.6, U10.4
unnamed: U8.3, U10.5
unnamed: U9.9, U10.8
unnamed: U9.11, U10.9
unnamed: U8.8, U10.10
unnamed: U9.2, U10.11
unnamed: U7.10, U19.4 (Y)

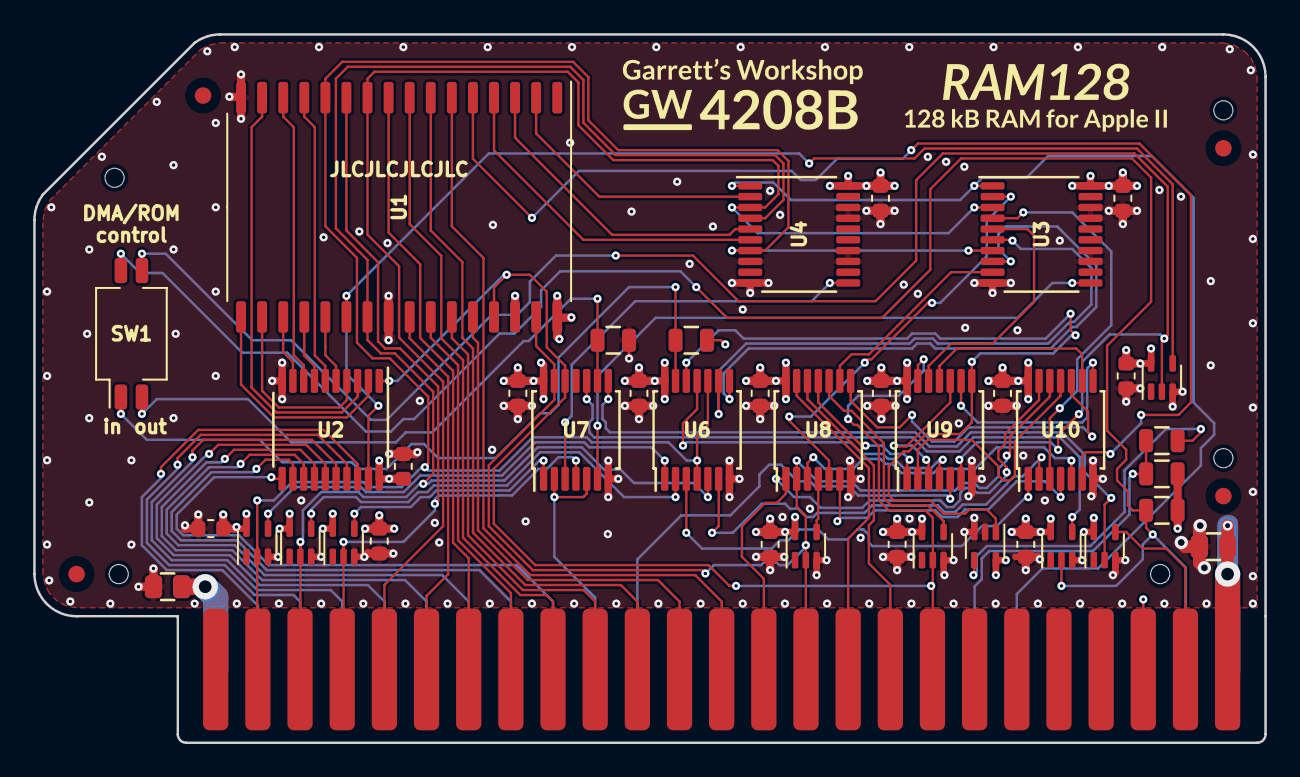
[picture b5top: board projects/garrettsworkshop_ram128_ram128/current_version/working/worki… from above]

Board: 4 copper layers, 74.2 x 42.7 mm, 50 parts (0 on the bottom side), 79 nets.
